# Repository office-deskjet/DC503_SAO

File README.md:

# DC503 SAO
KiCad and Arduino code for DC503's shitty addon.

## ART
has the vector art files

## FW
Has the Arduino code

## HW
Has the KiCad source file

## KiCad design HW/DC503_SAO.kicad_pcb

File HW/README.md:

# Notes
Made with KiCad 4.07 then upgraded to 5.0... I think.  

# Links
How to used KiCad:
https://www.youtube.com/watch?v=JN_Y93RTdSo&list=PLy2022BX6Eso532xqrUxDT1u2p4VVsg-q  
Help here:
https://forum.kicad.info/  

How to Charlieplex: https://www.instructables.com/id/Controlling-20-Leds-from-5-Arduino-pins-using-Cha/

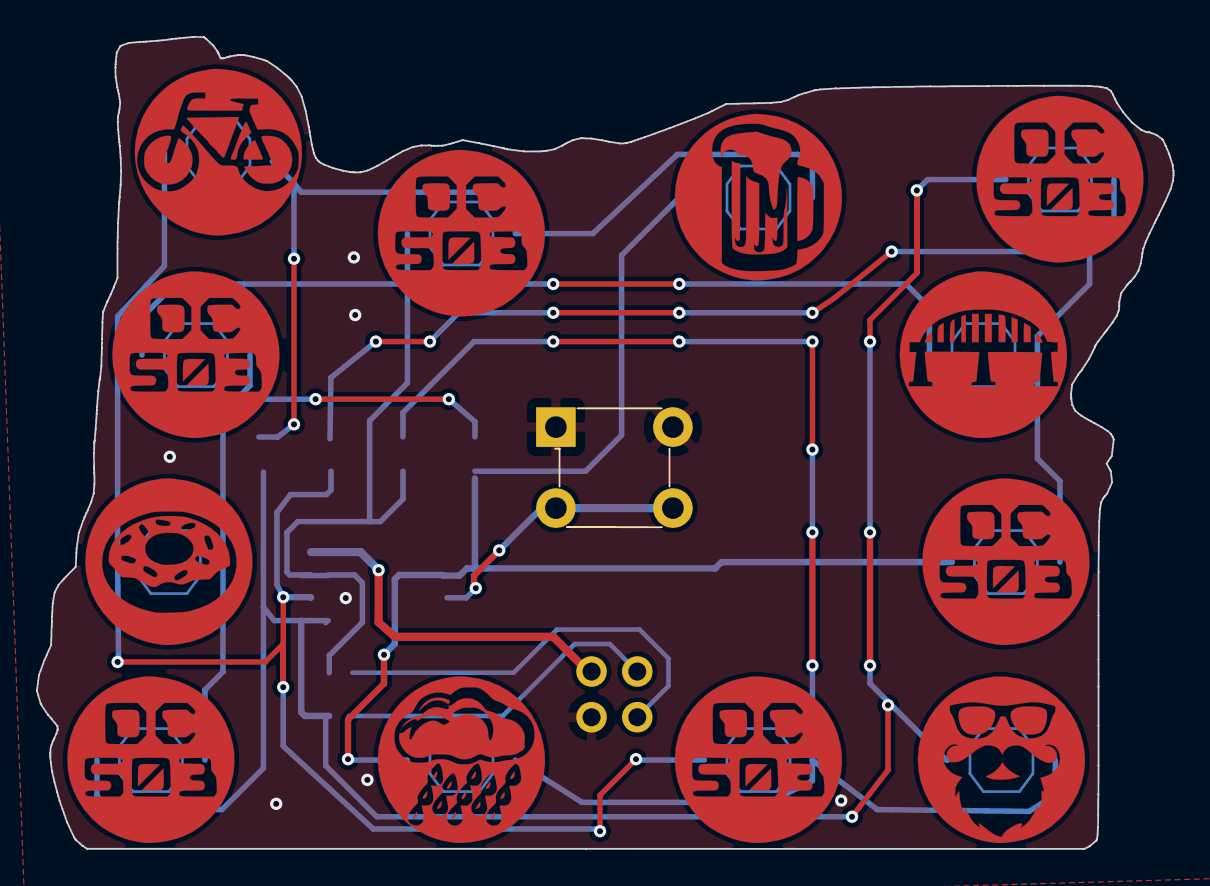
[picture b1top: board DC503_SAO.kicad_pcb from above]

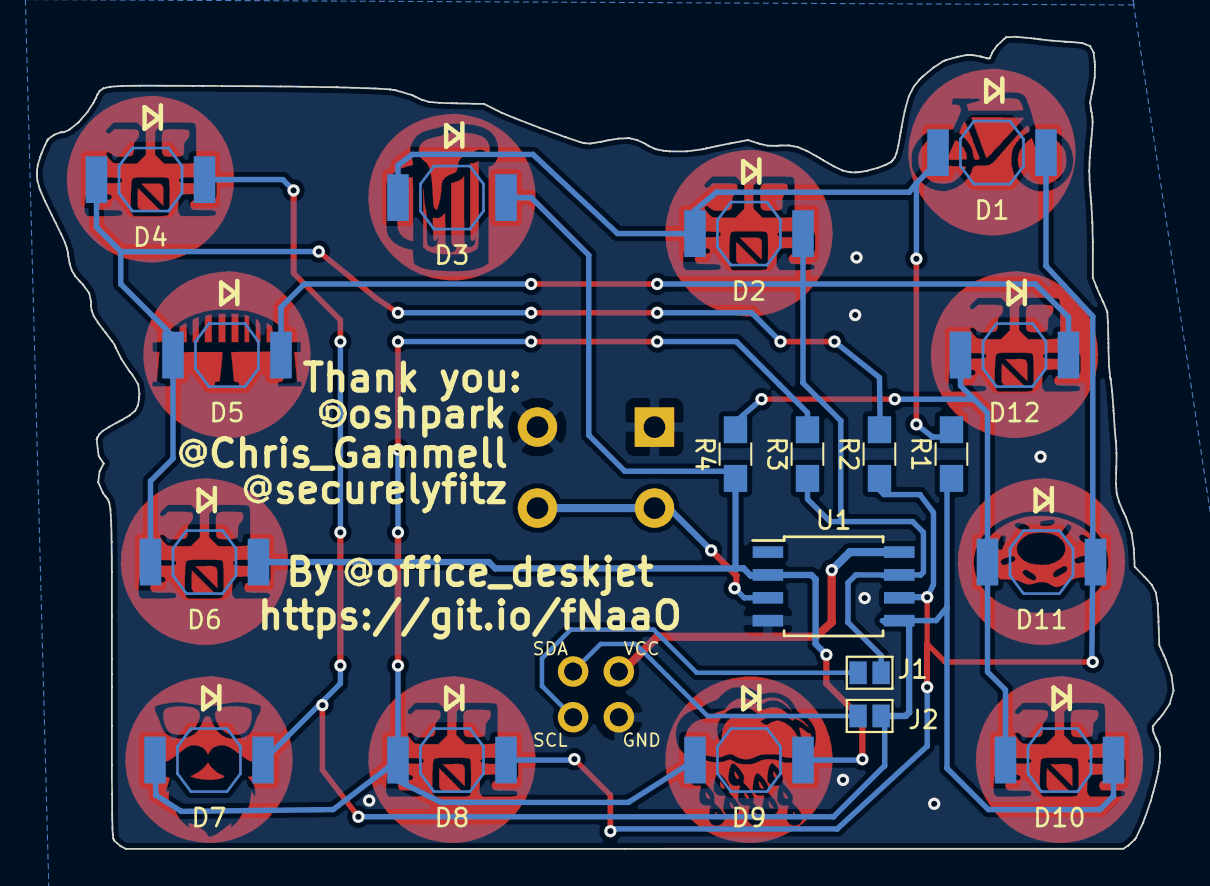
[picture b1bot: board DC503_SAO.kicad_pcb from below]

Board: 2 copper layers, 63.1 x 45.1 mm, 21 parts (7 on the bottom side), 13 nets.

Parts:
D1, D2, D3, D4, D5, D6, D7, D8, D9, D10, D11, D12: LED; OSRAM_LED
J1, J2: GS2
R1, R2, R3, R4: 100R; R_0805_HandSoldering
S1: 1825910-6; Switch_Tactile_THT_6x6mm
U1: ATTINY85-20SU; SOIJ-8_5.3x5.3mm_Pitch1.27mm
X1: Badgelife_shitty_connector; Badgelife-Shitty-2x2

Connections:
+3V3: U1.8, X1.1
/BUTTON: S1.3, S1.4, U1.3
/ROW1: D4.1, D7.1, D10.1, J2.1, R1.1, U1.5
/ROW2: D1.1, D8.1, D11.1, R2.1, U1.6
/ROW3: D2.1, D5.1, D12.1, J1.1, R3.1, U1.7
/ROW4: D3.1, D6.1, D9.1, R4.1, U1.2
/ROW_1: D1.2, D2.2, D3.2, R1.2
/ROW_2: D4.2, D5.2, D6.2, R2.2
/ROW_3: D7.2, D8.2, D9.2, R3.2
/ROW_4: D10.2, D11.2, D12.2, R4.2
GND: S1.1, S1.2, U1.4, X1.2
unnamed: J1.2, X1.3
unnamed: J2.2, X1.4

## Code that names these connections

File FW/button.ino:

#define ROW1 0
#define ROW2 1
#define ROW3 2
#define ROW4 3

#define BUTTON A2

void setup()
{
  // high Z for all pins
  pinMode(ROW1, INPUT);
  pinMode(ROW2, INPUT);
  pinMode(ROW3, INPUT);
  pinMode(ROW4, INPUT);
  
  pinMode(BUTTON, INPUT_PULLUP);
}

void loop()
{

  if (digitalRead(BUTTON) == LOW) {
    pinMode(ROW1, OUTPUT);
    pinMode(ROW2, OUTPUT);
    digitalWrite(ROW1, HIGH);
    digitalWrite(ROW2, LOW);
  }
  else
  {
    pinMode(ROW1, INPUT);
    pinMode(ROW2, INPUT);
  }
}

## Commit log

2018-07-18 Added all the parts to the schematic
2018-07-18 add ignore file and KiCad file
2018-07-18 wired up SOA connector, switch, and three LEDs
2018-07-18 finished LEDs
2018-07-18 starting footprint for LED
2018-07-19 Added Footprint for LED Added footprints to parts Generated Netlist
2018-07-19 Fixed footprint issue by adding footprints to PCBnew
2018-07-21 added board outline
2018-07-22 fixed schematic library import, add code for LED pattern states.
2018-07-22 fixed footprint to back of board
2018-07-22 moved parts to back layer. Connected I2C pins (not ideally)
2018-07-22 updating stuff
2018-07-26 Adding code for button and cycling through states, not done
2018-07-26 move it from directory
2018-07-26 Adding all the art work
2018-07-26 added DC503 art
2018-07-26 moving leds
2018-07-26 Fixed up readme.md
2018-07-26 links for KiCad art
2018-07-26 formatting
2018-07-26 added another blog
2018-07-26 Fixed LED footpint to include no copper and no solder mask regions
2018-07-26 moved the Diode symbole down on footprint, updated PCB layout.
2018-07-26 more helpfull links
2018-07-28 Adding art footprints
2018-07-28 cleaning up art files, changed process to do svg to bmp to kicad
2018-07-28 beard, dc503 art
2018-07-28 Got the art done. organized art directory
2018-07-28 Adding artwork files
2018-07-28 Template for making art
2018-07-28 Footprints for top layer art
2018-07-28 finialized art
2018-07-28 moving LED's arround, top layer art done
2018-07-30 Removed Silk screen from SAO CX placed LEDs move LED ref silk
2018-07-30 Fixed D12 wiring, Added Labels to LED nets
2018-07-30 updated LED mapping to reflect schematic
2018-07-30 Fixed the LED footprint silk for the correct polarity. Layout updated with correct footprints
2018-07-30 Updated Resistor refs to match their row number
2018-07-30 Added traces to resistors
2018-07-30 updated the LED footprint to use poly, not circle, Add traces for resistors
2018-07-30 Bottom gnd fill, added ROW_X traces
2018-07-30 Updated gnd plane on bottom side, connecting LEDs
2018-07-30 ROW1 and ROW_1 done. Updated gnd vias.
2018-07-30 ROW3 and ROW_3 done.
2018-07-30 ROW4 and ROW_4 done. touch up on other rows
2018-07-30 finishing ground pours on back. KiCad keeps removing the vias from gnd connection
2018-07-30 Gerbber file for stencil
2018-07-30 Had a F.Cu trace on DC503 art, fixed gnd vias again >:(
2018-08-03 adding schematic PDF, adding Debugging program to fix LED lighting
2018-08-03 D1 - D5 working
2018-08-03 All LEDs work EXCEPT D7 D8 D9
2018-08-04 got all the LEDs working on new board. Previous board had a short to ground on R3
2018-08-04 So the debug code is not necissary on a good board. The regualr charlie-plexing code works fine!
2018-08-05 got interrupt and debuce working
2018-08-05 moveing code around.:
2018-08-05 Finialized FW code Added README documentation Fixed the LED footprint to keepout copper! Fixed silk screen for at sign Fixed ground vias....again....
2018-08-21 Changed resistor and tiny85 foot prints. Roated SAO connector and fixed traces. Still missing ground vias.
2018-08-28 added link to charlieplex
2018-08-28 Updatedd files to KiCad 5.0. Added heart back to top.
2018-08-28 adding symbol table
2018-09-01 added beard svg
2018-11-04 uploading finihsed picutre
2018-11-04 fix spelling
